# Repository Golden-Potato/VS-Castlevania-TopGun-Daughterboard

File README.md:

# VS-Castlevania-TopGun-Daughterboard
https://github.com/Golden-Potato/VS-Castlevania-TopGun-Daughterboard

KiCad PCB files to create a reproduction VS Castlevania / VS Topgun daughterboard.  Have it made by your preferred PCB fab. I use http://aisler.net

This design has one minor improvement to avoid bus conflicts that were present on the original Konami design.

The bank switching scheme Konami implemented in the original NES version of Castlevania to address a 128k ROM was dubbed UNROM by the NES emulation community.
https://wiki.nesdev.com/w/index.php/UxROM
It suffered from data bus conflicts during bank switching as the CPU will write data to the bus while the ROM is still writing data to the bus.  Although this conflict was easy to avoid from a hardware standpoint, these game cartridges were to be mass produced, and it was imperative to have as small of a chip count as possible.  Rather than add another IC, Konami got around the conflict by storing the same data in ROM at the addresses being written to by the CPU as the data the CPU was trying to write.  This means that while the CPU and ROM were writing data to the bus at the same time, it was the same data.

This works fine unless the ROM becomes corrupt which can easily happen to the arcade version if programmed on a UV erasable EPROM.  If the data from the ROM and the data being written by the CPU differed, there is a risk of overloading the CPU's data port.

Comparing the original cartridge design with the schematic for VS Topgun daughterboard (located in the manual), it's apparent Konami recycled their design for bank switching the ROM with the exception of some minor changes required for the differences in hardware between the VS system and the NES.  One of the additional ICs present on the VS daughterboard is a quad 2-input NAND gate, and not all of the instances of the IC were used.  This design uses one additional instance of the NAND gate as an inverter to feed the ROM IC's /OE from the CPU's R/W pin which prevents the ROM from writing to the bus when the CPU is writing.

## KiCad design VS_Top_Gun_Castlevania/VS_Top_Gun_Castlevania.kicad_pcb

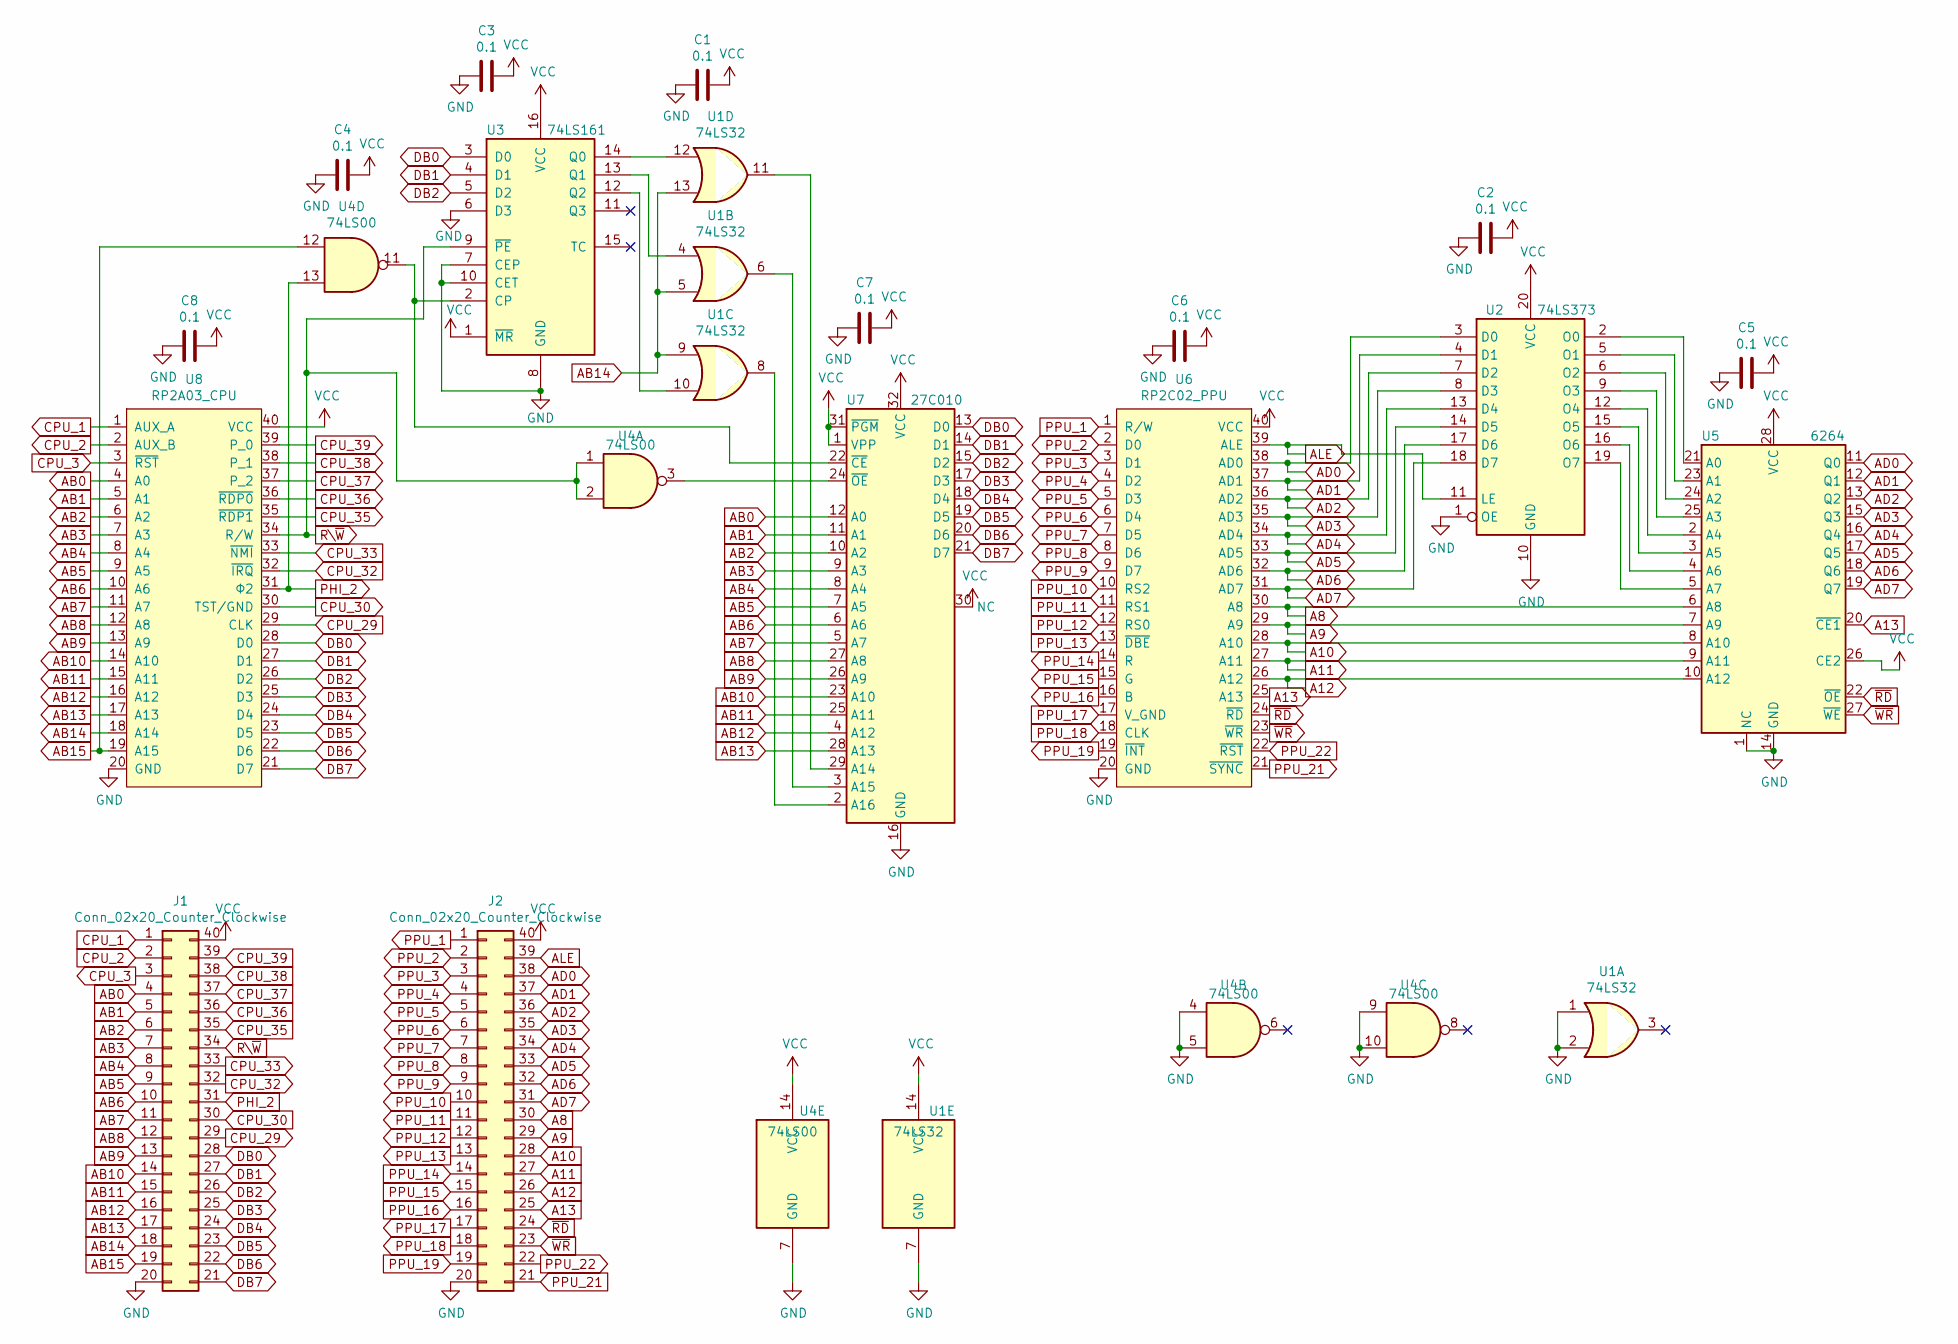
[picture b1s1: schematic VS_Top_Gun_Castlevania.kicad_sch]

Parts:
C1, C2, C3, C4, C5, C6, C7, C8: 0.1; C_Disc_D12.5mm_W5.0mm_P7.50mm
J1, J2: Conn_02x20_Counter_Clockwise; DIP-40_W15.24mm_Socket
U1: 74LS32; DIP-14_W7.62mm_Socket
U2: 74LS373; DIP-20_W7.62mm_Socket
U3: 74LS161; DIP-16_W7.62mm_Socket
U4: 74LS00; DIP-14_W7.62mm_Socket
U5: 6264; DIP-28_W15.24mm_Socket
U6: RP2C02_PPU; DIP-40_W15.24mm_Socket
U7: 27C010; DIP-32_W15.24mm_Socket
U8: RP2A03_CPU; DIP-40_W15.24mm_Socket

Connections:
A8: J2.30, U5.6 (A8), U6.30 (A8)
A9: J2.29, U5.7 (A9), U6.29 (A9)
A10: J2.28, U5.8 (A10), U6.28 (A10)
A11: J2.27, U5.9 (A11), U6.27 (A11)
A12: J2.26, U5.10 (A12), U6.26 (A12)
A13: J2.25, U5.20 (~CE1), U6.25 (A13)
AB0: J1.4, U7.12 (A0), U8.4 (A0)
AB1: J1.5, U7.11 (A1), U8.5 (A1)
AB2: J1.6, U7.10 (A2), U8.6 (A2)
AB3: J1.7, U7.9 (A3), U8.7 (A3)
AB4: J1.8, U7.8 (A4), U8.8 (A4)
AB5: J1.9, U7.7 (A5), U8.9 (A5)
AB6: J1.10, U7.6 (A6), U8.10 (A6)
AB7: J1.11, U7.5 (A7), U8.11 (A7)
AB8: J1.12, U7.27 (A8), U8.12 (A8)
AB9: J1.13, U7.26 (A9), U8.13 (A9)
AB10: J1.14, U7.23 (A10), U8.14 (A10)
AB11: J1.15, U7.25 (A11), U8.15 (A11)
AB12: J1.16, U7.4 (A12), U8.16 (A12)
AB13: J1.17, U7.28 (A13), U8.17 (A13)
AB14: J1.18, U1.5, U1.9, U1.13, U8.18 (A14)
AB15: J1.19, U4.12, U8.19 (A15)
AD0: J2.38, U2.3 (D0), U5.11 (Q0), U6.38 (AD0)
AD1: J2.37, U2.4 (D1), U5.12 (Q1), U6.37 (AD1)
AD2: J2.36, U2.7 (D2), U5.13 (Q2), U6.36 (AD2)
AD3: J2.35, U2.8 (D3), U5.15 (Q3), U6.35 (AD3)
AD4: J2.34, U2.13 (D4), U5.16 (Q4), U6.34 (AD4)
AD5: J2.33, U2.14 (D5), U5.17 (Q5), U6.33 (AD5)
AD6: J2.32, U2.17 (D6), U5.18 (Q6), U6.32 (AD6)
AD7: J2.31, U2.18 (D7), U5.19 (Q7), U6.31 (AD7)
ALE: J2.39, U2.11 (LE), U6.39 (ALE)
CPU_1: J1.1, U8.1 (AUX_A)
CPU_2: J1.2, U8.2 (AUX_B)
CPU_3: J1.3, U8.3 (~RST)
CPU_29: J1.29, U8.29 (CLK)
CPU_30: J1.30, U8.30 (TST/GND)
CPU_32: J1.32, U8.32 (~IRQ)
CPU_33: J1.33, U8.33 (~NMI)
CPU_35: J1.35, U8.35 (~RDP1)
CPU_36: J1.36, U8.36 (~RDP0)
CPU_37: J1.37, U8.37 (P_2)
CPU_38: J1.38, U8.38 (P_1)
CPU_39: J1.39, U8.39 (P_0)
DB0: J1.28, U3.3 (D0), U7.13 (D0), U8.28 (D0)
DB1: J1.27, U3.4 (D1), U7.14 (D1), U8.27 (D1)
DB2: J1.26, U3.5 (D2), U7.15 (D2), U8.26 (D2)
DB3: J1.25, U7.17 (D3), U8.25 (D3)
DB4: J1.24, U7.18 (D4), U8.24 (D4)
DB5: J1.23, U7.19 (D5), U8.23 (D5)
DB6: J1.22, U7.20 (D6), U8.22 (D6)
DB7: J1.21, U7.21 (D7), U8.21 (D7)
GND: C1.1, C2.1, C3.1, C4.1, C5.1, C6.1, C7.1, C8.1, J1.20, J2.20, U1.1, U1.2, U1.7 (GND), U2.1 (OE), U2.10 (GND), U3.6 (D3), U3.7 (CEP), U3.8 (GND), U3.10 (CET), U4.4, U4.5, U4.7 (GND), U4.9, U4.10, U5.1 (NC), U5.14 (GND), U6.20 (GND), U7.16 (GND), U8.20 (GND)
unnamed: U2.2 (O0), U5.21 (A0)
unnamed: U2.5 (O1), U5.23 (A1)
unnamed: U2.6 (O2), U5.24 (A2)
unnamed: U2.9 (O3), U5.25 (A3)
unnamed: U2.12 (O4), U5.2 (A4)
unnamed: U2.15 (O5), U5.3 (A5)
unnamed: U2.16 (O6), U5.4 (A6)
unnamed: U2.19 (O7), U5.5 (A7)
unnamed: U3.2 (CP), U4.11, U7.22 (~CE)
unnamed: U1.12, U3.14 (Q0)
unnamed: U1.4, U3.13 (Q1)
unnamed: U1.10, U3.12 (Q2)
unnamed: U1.11, U7.29 (A14)
unnamed: U1.6, U7.3 (A15)
unnamed: U1.8, U7.2 (A16)
unnamed: U4.3, U7.24 (~OE)
PHI_2: J1.31, U4.13, U8.31 (Φ2)
PPU_1: J2.1, U6.1 (R/W)
PPU_2: J2.2, U6.2 (D0)
PPU_3: J2.3, U6.3 (D1)
PPU_4: J2.4, U6.4 (D2)
PPU_5: J2.5, U6.5 (D3)
PPU_6: J2.6, U6.6 (D4)
PPU_7: J2.7, U6.7 (D5)
PPU_8: J2.8, U6.8 (D6)
PPU_9: J2.9, U6.9 (D7)
PPU_10: J2.10, U6.10 (RS2)
PPU_11: J2.11, U6.11 (RS1)
PPU_12: J2.12, U6.12 (RS0)
PPU_13: J2.13, U6.13 (~DBE)
PPU_14: J2.14, U6.14 (R)
PPU_15: J2.15, U6.15 (G)
PPU_16: J2.16, U6.16 (B)
PPU_17: J2.17, U6.17 (V_GND)
PPU_18: J2.18, U6.18 (CLK)
PPU_19: J2.19, U6.19 (~INT)
PPU_21: J2.21, U6.21 (~SYNC)
PPU_22: J2.22, U6.22 (~RST)
R\~W: J1.34, U3.9 (~PE), U4.1, U4.2, U8.34 (R/W)
VCC: C1.2, C2.2, C3.2, C4.2, C5.2, C6.2, C7.2, C8.2, J1.40, J2.40, U1.14 (VCC), U2.20 (VCC), U3.1 (~MR), U3.16 (VCC), U4.14 (VCC), U5.26 (CE2), U5.28 (VCC), U6.40 (VCC), U7.1 (VPP), U7.31 (~PGM), U7.32 (VCC), U8.40 (VCC)
~RD: J2.24, U5.22 (~OE), U6.24 (~RD)
~WR: J2.23, U5.27 (~WE), U6.23 (~WR)

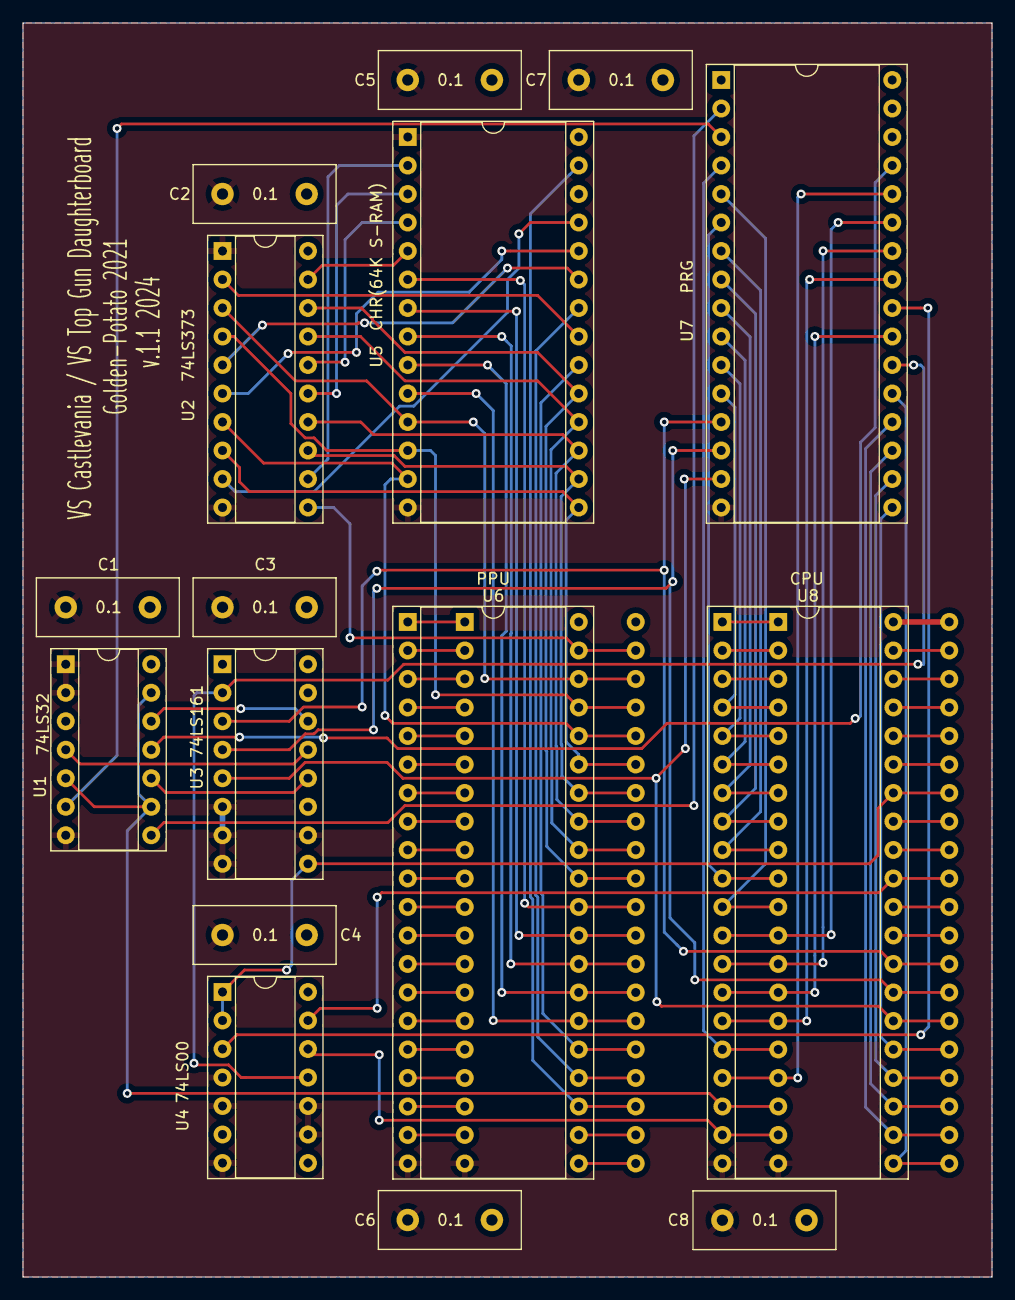
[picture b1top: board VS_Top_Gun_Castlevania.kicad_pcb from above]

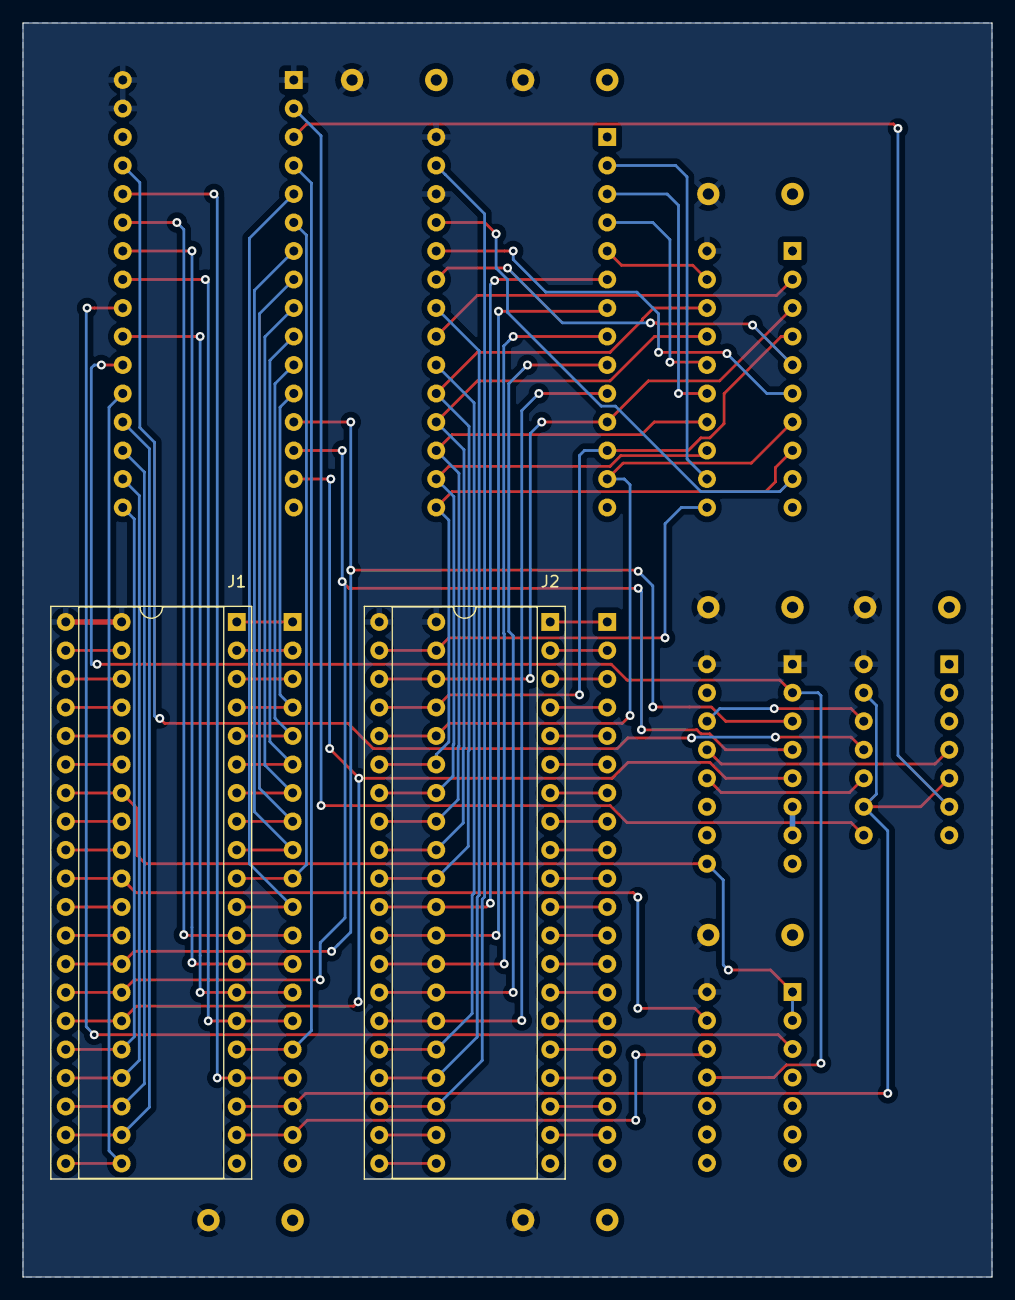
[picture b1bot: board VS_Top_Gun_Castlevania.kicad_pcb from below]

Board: 2 copper layers, 86.4 x 111.8 mm, 18 parts (2 on the bottom side), 94 nets.

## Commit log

2024-09-27 v1.1
    Connected all unused inputs to ground on logic ICs to prevent unexpected behavior
